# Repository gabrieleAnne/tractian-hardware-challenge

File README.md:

# Desafio de Hardware TRACTIAN · Tech Fast Track 2026

Projeto que desenvolvi no desafio técnico de hardware do processo **Tech Fast Track 2026** da TRACTIAN.

## Escopo

O desafio teve duas etapas.

### Task 1: pré-projeto de um sistema de aquisição multicanal de sinais

Documento: [`task1-pre-projeto/`](task1-pre-projeto/)

- Arquitetura do sistema e diagrama de blocos funcionais
- Escolha de circuitos integrados comerciais para cada bloco, com justificativa
- Interfaces de comunicação
- Robustez para ambiente industrial: isolação, proteção e alimentação

### Task 2: placement de componentes de um conversor DC/DC buck 24 V para 5 V (20 A)

Projeto KiCad: [`task2-pcb-placement/`](task2-pcb-placement/)

- Loops de alta corrente minimizados
- Estágio de potência separado do controle
- Integridade dos sinais sensíveis: feedback, compensação e sense de corrente
- Menos EMI e menos efeitos parasitas

## Principais decisões de projeto

- MOSFETs agrupados de forma compacta para reduzir o loop de comutação
- Indutor perto do nó SW
- Capacitores de entrada e de saída agrupados para responder bem a transientes
- Rede de feedback e compensação perto do controlador
- Gate drive com trilhas curtas (R1 e R8)
- Bootstrap e redes auxiliares perto do U1

O layout equilibra a área disponível na placa, a proximidade elétrica, a separação funcional e a legibilidade.

## Ferramentas

- KiCad 9

## Observação

O enunciado do desafio pertence à TRACTIAN e não está neste repositório. O esquemático do conversor veio do projeto inicial fornecido no desafio; o posicionamento dos componentes na placa e o pré-projeto da Task 1 são trabalho meu.

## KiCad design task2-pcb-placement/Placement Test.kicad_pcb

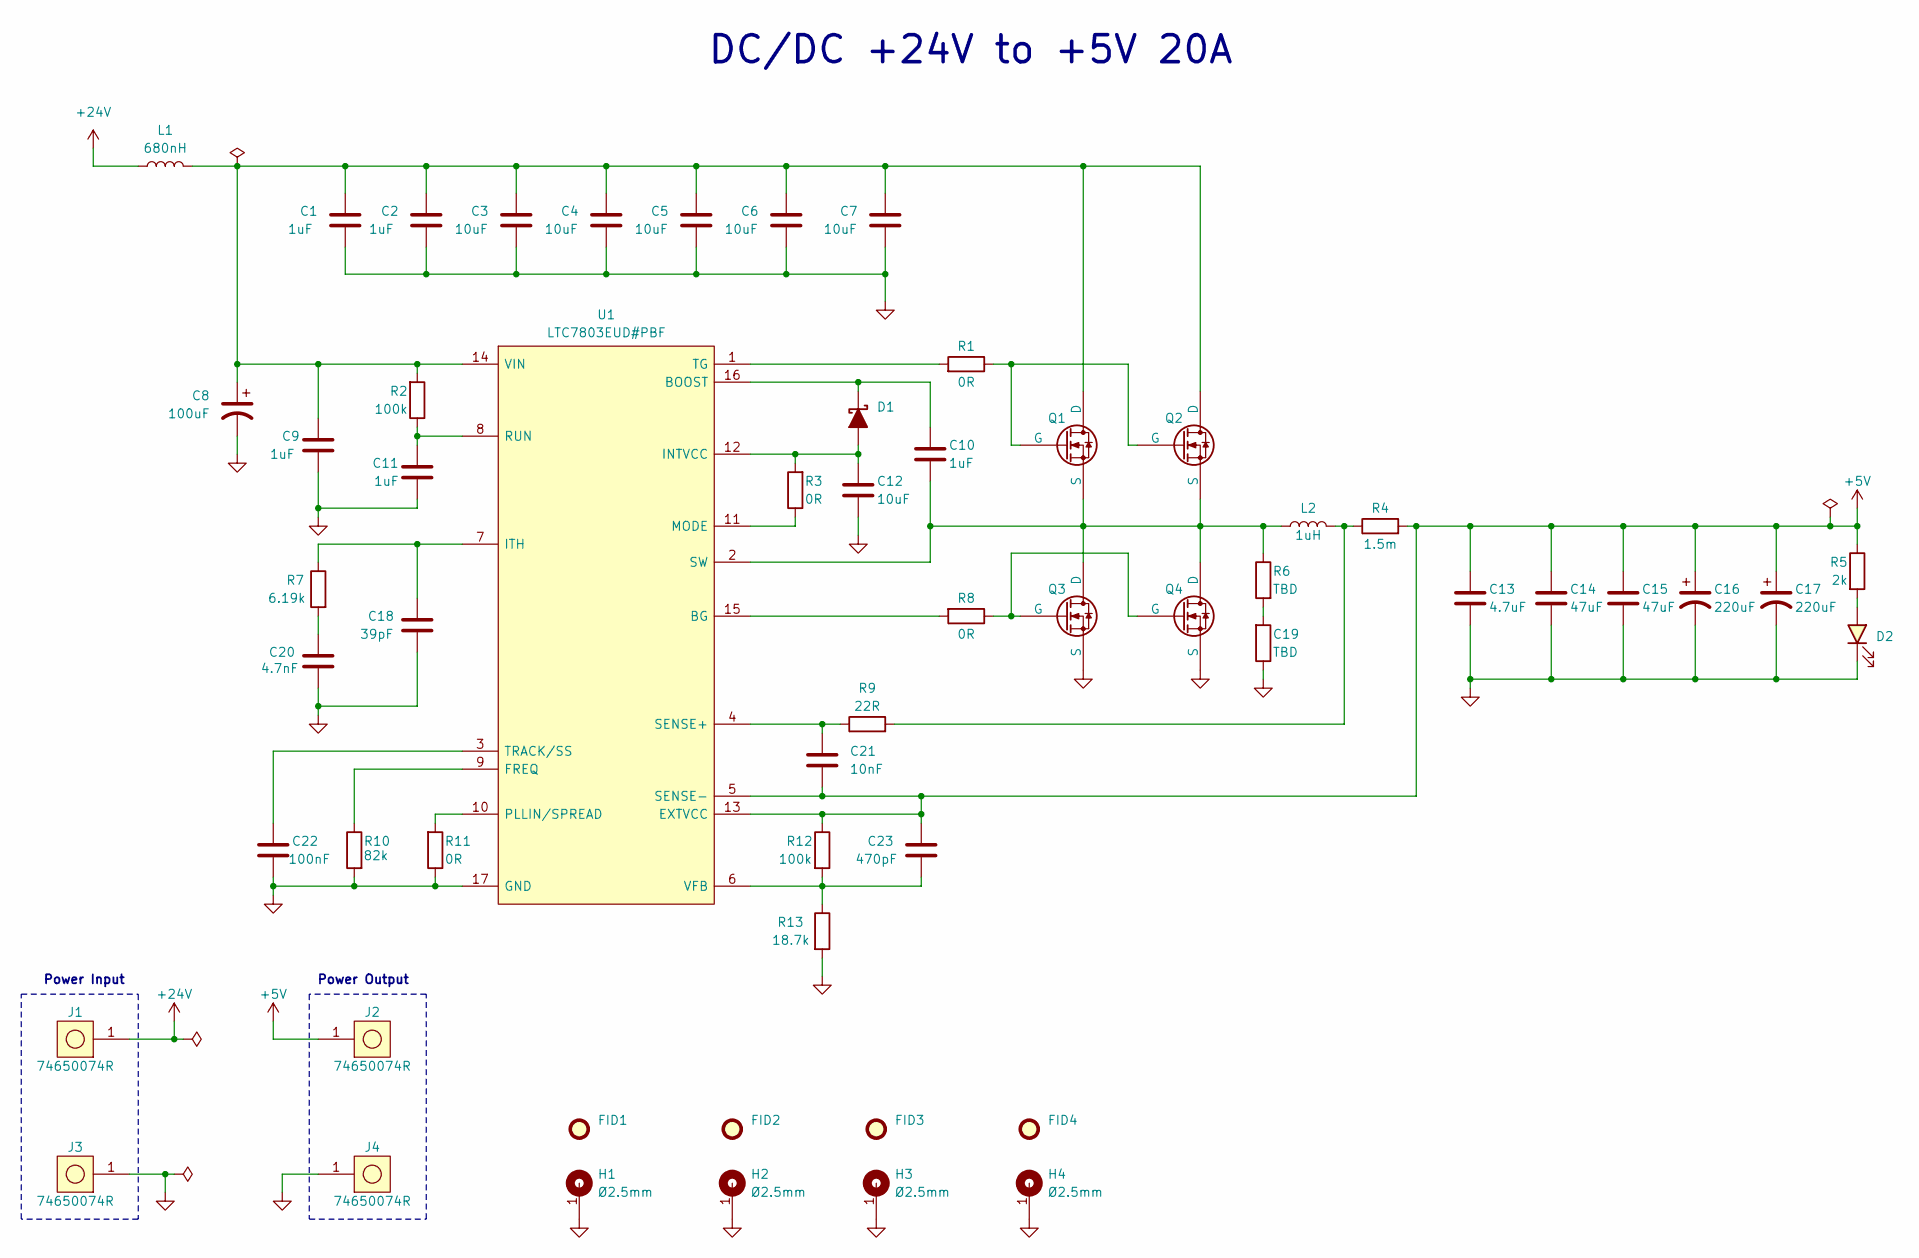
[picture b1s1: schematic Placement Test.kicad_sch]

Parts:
C1, C2, C9, C11: 1uF-0805_02; Capacitor_0805
C3, C4, C5, C6, C7: 10uF-0805_01; Capacitor_0805
C8: 100uF-8.3x8.3x6.7_01; A768KE; Part Number A768KE107M1VLAE036
C10: 1uF-0402_01; Capacitor_0402
C12: 10uF-0402_01; Capacitor_0402
C13: 4.7uF-1206_02; Capacitor_1206
C14, C15: 47uF-0805_01; Capacitor_0805
C16, C17: 220uF-8.3x8.3x6.7_01; A768KE; Part Number A768KE227M1DLAE029
C18: 39pF-0402_01; Capacitor_0402
C19: TBD-1206; Resistor_1206; Part Number NA
C20: 4.7nF-0402_01; Capacitor_0402
C21: 10nF-0402_01; Capacitor_0402
C22: 100nF-0402_02; Capacitor_0402
C23: 470pF-0402_01; Capacitor_0402
D1: BAS40HYT116; SOT23-3_P0.95_2.92x1.3x1.12; Part Number BAS40HYT116
D2: 150040BS73240; LED_0402; Part Number 150040BS73240
FID1, FID2, FID3, FID4: Fiducial_Copper-D1mm_Mask-D2mm
H1, H2, H3, H4: MountingHole_2.5mm_PAD_5mm; MountingHole_2.5mm_PAD-5mm
J1, J2, J3, J4: 74650074R; Part Number 74650074R
L1: 680nH-4.1x4.1x1.9_01; SRP4020FA; Part Number SRP4020FA-R68M
L2: 1uH-12.5x12.5x6.2_01; SRP1265A
Q1, Q2, Q3, Q4: BSC014N04LSI; TDSON-8-FL_P1.27_5.075x5.9x1.05; Part Number BSC014N04LSI
R1, R3, R8, R11: 0R-0402_01; Resistor_0402
R2: 100k-0402_01; Resistor_0402
R4: 1.5m-1225_01; Resistor_1225
R5: 2k-0402_01; Resistor_0402
R6: TBD-1206; Resistor_1206; Part Number NA
R7: 6.19k-0402_01; Resistor_0402
R9: 22R-0402_01; Resistor_0402
R10: 82k-0402_01; Resistor_0402
R12: 100k-0402_02; Resistor_0402
R13: 18.7k-0402_01; Resistor_0402
U1: LTC7803EUD#PBF; VQFN-16-1EP_P0.5_3x3x0.9; Part Number LTC7803EUD#PBF

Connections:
+5V: C13.1, C14.1, C15.1, C16.1, C17.1, C21.2, C23.1, J2.1, R4.2, R5.2, R12.2, U1.5 (SENSE-), U1.13 (EXTVCC)
+24V: J1.1, L1.1
GND: C1.2, C2.2, C3.2, C4.2, C5.2, C6.2, C7.2, C8.2, C9.2, C11.2, C12.2, C13.2, C14.2, C15.2, C16.2, C17.2, C18.2, C19.2, C20.2, C22.2, D2.1 (Cathode), H1.1, H2.1, H3.1, H4.1, J3.1, J4.1, Q3.1 (S), Q3.2 (S), Q3.3 (S), Q4.1 (S), Q4.2 (S), Q4.3 (S), R10.1, R11.1, R13.1, U1.17 (GND)
unnamed: C19.1, R6.1
unnamed: C20.1, R7.1
unnamed: C12.1, D1.1 (Anode), R3.2, U1.12 (INTVCC)
unnamed: C10.1, D1.3 (Cathode), U1.16 (BOOST)
unnamed: D2.2 (Anode), R5.1
unnamed: L2.2, R4.1, R9.2
unnamed: Q1.4 (G), Q2.4 (G), R1.1
unnamed: Q3.4 (G), Q4.4 (G), R8.1
unnamed: R8.2, U1.15 (BG)
unnamed: R10.2, U1.9 (FREQ)
unnamed: C18.1, R7.2, U1.7 (ITH)
unnamed: R3.1, U1.11 (MODE)
unnamed: R11.2, U1.10 (PLLIN/SPREAD)
unnamed: C11.1, R2.1, U1.8 (RUN)
unnamed: C21.1, R9.1, U1.4 (SENSE+)
unnamed: C10.2, L2.1, Q1.1 (S), Q1.2 (S), Q1.3 (S), Q2.1 (S), Q2.2 (S), Q2.3 (S), Q3.5 (D), Q3.6 (D), Q3.7 (D), Q3.8 (D), Q4.5 (D), Q4.6 (D), Q4.7 (D), Q4.8 (D), R6.2, U1.2 (SW)
unnamed: R1.2, U1.1 (TG)
unnamed: C22.1, U1.3 (TRACK/SS)
unnamed: C23.2, R12.1, R13.2, U1.6 (VFB)
unnamed: C1.1, C2.1, C3.1, C4.1, C5.1, C6.1, C7.1, C8.1, C9.1, L1.2, Q1.5 (D), Q1.6 (D), Q1.7 (D), Q1.8 (D), Q2.5 (D), Q2.6 (D), Q2.7 (D), Q2.8 (D), R2.2, U1.14 (VIN)

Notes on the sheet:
Power Output
DC/DC +24V to +5V 20A
Power Input

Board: 2 copper layers, 57 parts (0 on the bottom side), 23 nets, no tracks yet.

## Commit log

2026-03-29 Desafio de hardware TRACTIAN Tech Fast Track 2026: pre-projeto e placement da PCB
